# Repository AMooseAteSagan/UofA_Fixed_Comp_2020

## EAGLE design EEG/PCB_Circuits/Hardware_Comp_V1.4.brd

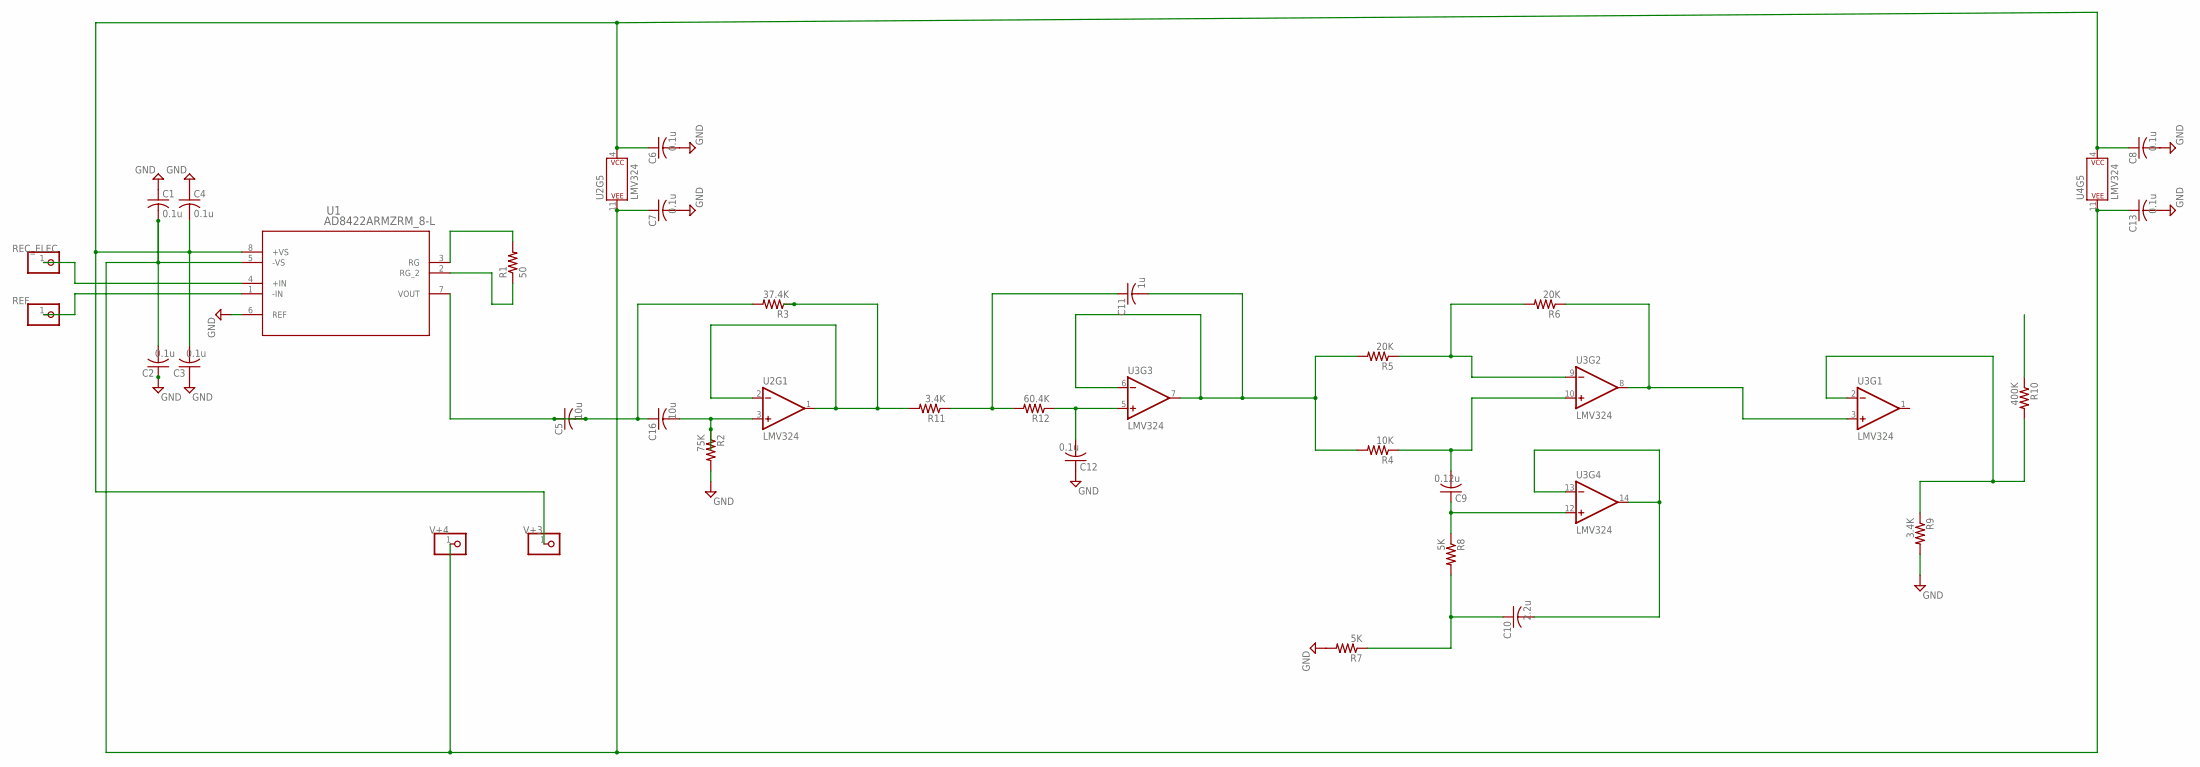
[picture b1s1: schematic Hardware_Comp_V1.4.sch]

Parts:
9V-: PINHD-1X1; 1X01
C1, C2, C3, C4, C6, C7, C8, C12, C13: 0.1u; C0603
C5, C16: 10u; C0603
C9: 0.12u; C0603
C10: 2.2u; C0603
C11: 1u; C0603
JP1, JP2, JP3: PINHD-1X1; 1X01
R1: 50; R0603
R2: 75K; R0603
R3: 37.4K; R0603
R4: 10K; R0603
R5, R6: 20K; R0603
R7, R8: 5K; R0603
R9, R11: 3.4K; R0603
R10: 400K; R0603
R12: 60.4K; R0603
U1: AD8422ARMZRM_8-L; RM_8-L
U2, U3, U4: LMV324; SO14

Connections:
GND: C1.1, C2.1, C3.1, C4.1, C6.2, C7.2, C8.2, C12.1, C13.2, R2.2, R7.2, R9.2, U1.6 (REF)
unnamed: C5.1, C5.2, C16.1, R3.2, U1.7 (VOUT)
unnamed: R3.1, R11.2, U2.1 (OUT), U2.2 (-IN)
unnamed: C16.2, R2.1, U2.3 (+IN)
unnamed: R9.1, R10.2, U3.2 (-IN)
unnamed: R1.2, U1.3 (RG)
unnamed: R1.1, U1.2 (RG_2)
unnamed: R6.1, U3.3 (+IN), U3.8 (OUT)
unnamed: C10.2, U3.13 (-IN), U3.14 (OUT)
unnamed: R5.1, R6.2, U3.9 (-IN)
unnamed: C9.2, R4.1, U3.10 (+IN)
unnamed: C9.1, R8.1, U3.12 (+IN)
unnamed: C10.1, R7.1, R8.2
unnamed: C12.2, R12.1, U3.5 (+IN)
unnamed: C11.2, R4.2, R5.2, U3.6 (-IN), U3.7 (OUT)
unnamed: C11.1, R11.1, R12.2
REC_ELEC: JP1.1, U1.4 (+IN)
REF: JP2.1, U1.1 (-IN)
V+3: 9V-.1, C3.2, C4.2, C6.1, C8.1, U1.8 (+VS), U2.4 (P$V+), U4.4 (P$V+)
V+4: C1.2, C2.2, C7.1, C13.1, JP3.1, U1.5 (-VS), U2.11 (P$V-), U4.11 (P$V-)

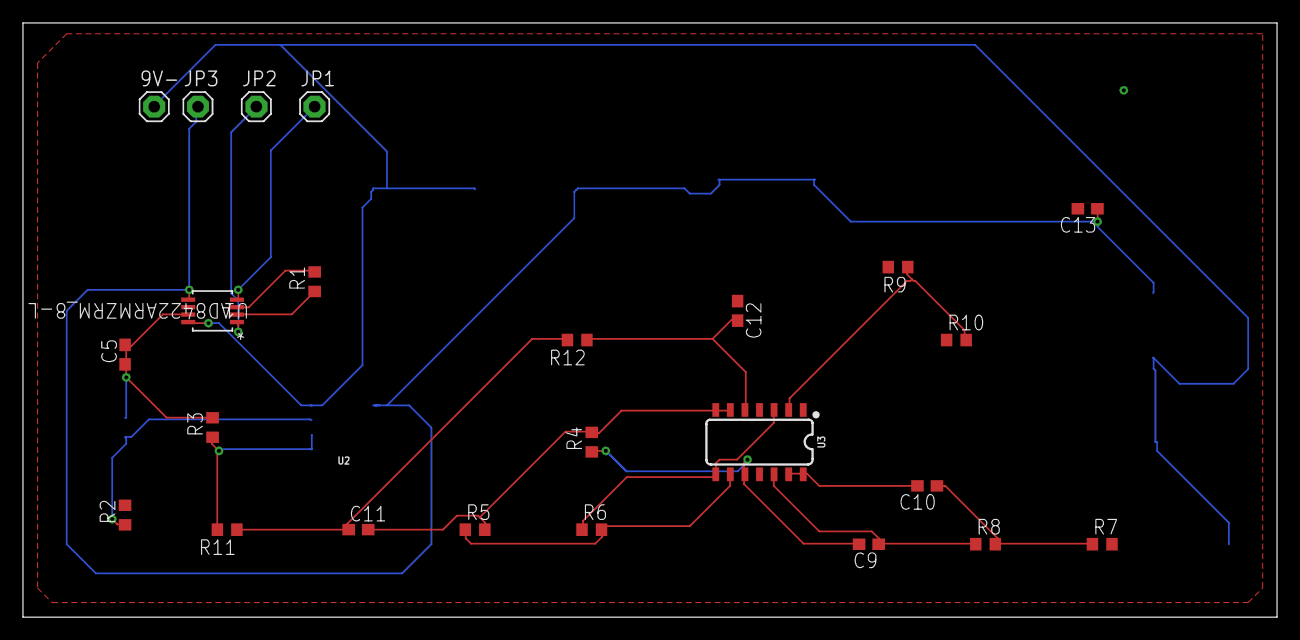
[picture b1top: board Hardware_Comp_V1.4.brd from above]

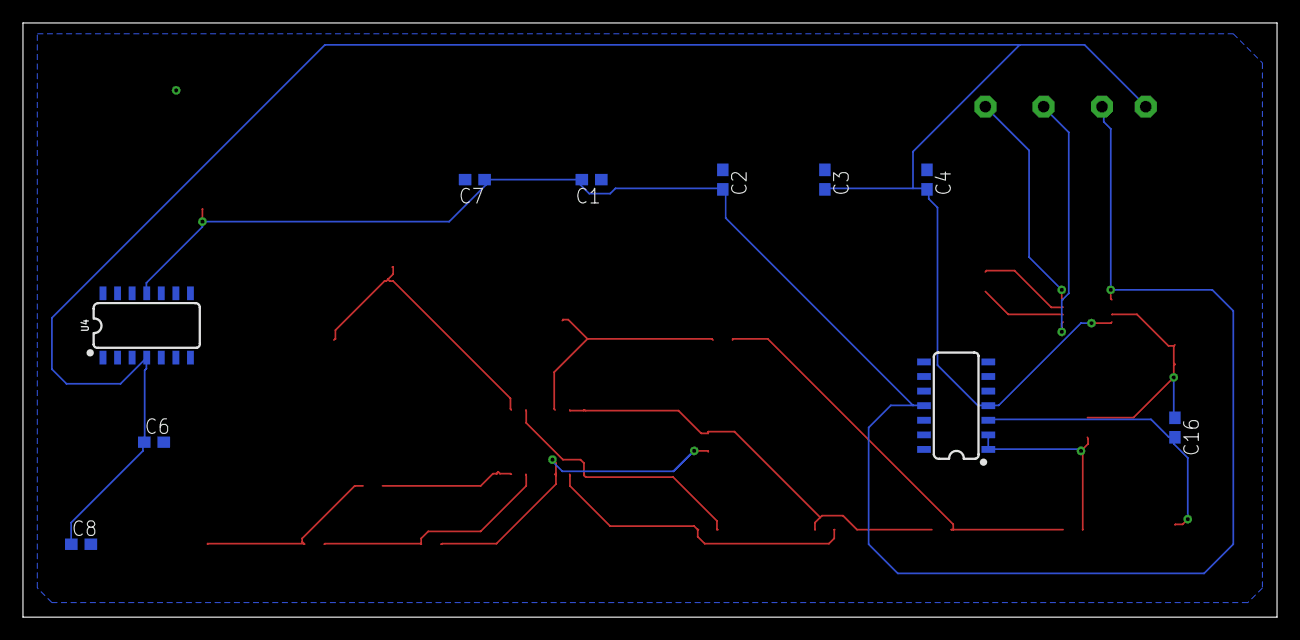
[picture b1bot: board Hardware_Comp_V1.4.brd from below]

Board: 2 copper layers, 109.2 x 51.7 mm, 34 parts (10 on the bottom side), 20 nets.

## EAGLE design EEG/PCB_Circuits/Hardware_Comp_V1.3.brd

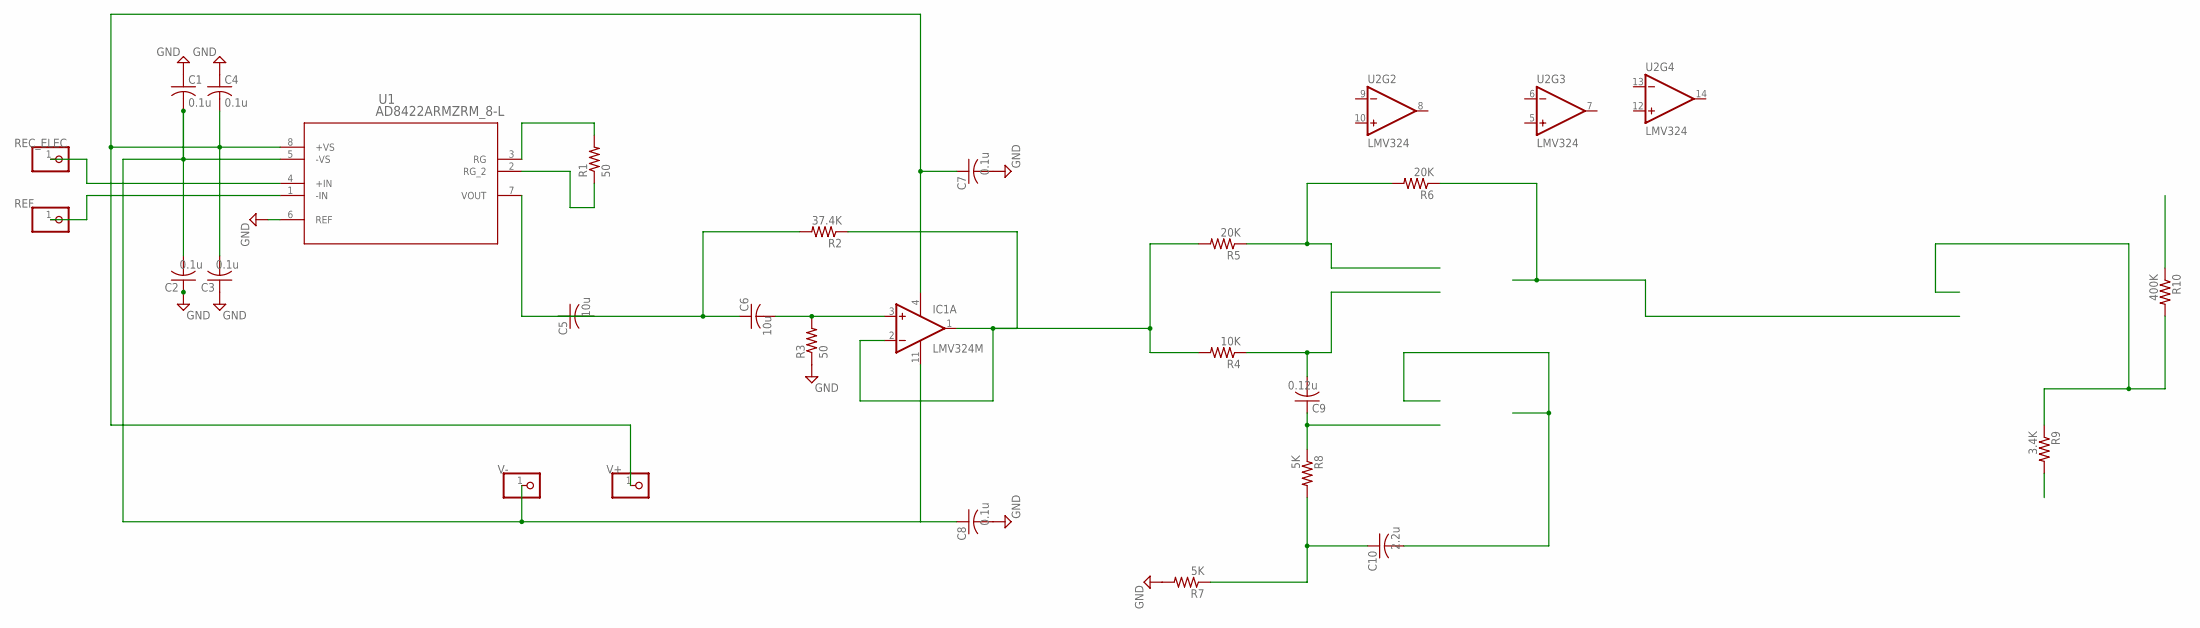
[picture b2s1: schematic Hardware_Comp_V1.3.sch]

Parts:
9V-: PINHD-1X1; 1X01
C1, C2, C3, C4, C7, C8: 0.1u; C0603
C5, C6: 10u; C0603
C9: 0.12u; C0603
C10: 2.2u; C0603
IC1: LMV324M; SO14
JP1, JP2, JP3: PINHD-1X1; 1X01
R1, R3: 50; R0603
R2: 37.4K; R0603
R4: 10K; R0603
R5, R6: 20K; R0603
R7, R8: 5K; R0603
R9: 3.4K; R0603
R10: 400K; R0603
U1: AD8422ARMZRM_8-L; RM_8-L
U2: LMV324; SO14

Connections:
GND: C1.1, C2.1, C3.1, C4.1, C7.2, C8.2, R3.1, R7.2, U1.6 (REF)
unnamed: C5.2, U1.7 (VOUT)
unnamed: C5.1, C6.1, R2.2
unnamed: C6.2, IC1.3 (+IN), R3.2
unnamed: R9.1, R10.2
unnamed: R1.2, U1.3 (RG)
unnamed: R1.1, U1.2 (RG_2)
unnamed: IC1.1 (OUT), IC1.2 (-IN), R2.1, R4.2, R5.2
unnamed: R5.1, R6.2
unnamed: C9.2, R4.1
unnamed: C9.1, R8.1
unnamed: C10.1, R7.1, R8.2
REC_ELEC: JP1.1, U1.4 (+IN)
REF: JP2.1, U1.1 (-IN)
V+: 9V-.1, C3.2, C4.2, C7.1, IC1.4 (V+), U1.8 (+VS)
V+1: C8.1
V-: C1.2, C2.2, IC1.11 (V-), JP3.1, U1.5 (-VS)

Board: 2 copper layers, 27 parts (0 on the bottom side), 16 nets, no tracks yet.

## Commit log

2020-03-09 removed debug
2020-03-09 Next_Version
2020-03-09 Version_4
2020-03-10 Created Board file for version 4
2020-03-10 fixed polygon
2020-03-12 added OpenCV requirement
2020-06-19 initial upload of eeg app with gui

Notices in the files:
parts and their libraries:
SparkFun-IC-Amplifiers: Licensing: Creative Commons ShareAlike 4.0 International - https://creativecommons.org/licenses/by-sa/4.0
